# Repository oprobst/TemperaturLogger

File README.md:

# TemperaturLogger

Einfacher Temperatur Logger über ATTiny 841 und Knopfzelle.
Gemessen wird über einen TSic 506, wofür die Spannung mittels DCDC Boost auf 5V gesetzt wird.

TODO:
Sobald der Logger an USB angeschlossen wird, kann er per Bootloader neu programmiert werden oder aber die Daten ausgelesen werden.

### Bootloader TinySafeBoot
http://jtxp.org/tech/tinysafeboot.htm
gute Anleitung unter https://ladvien.github.io/robots/tsb/

./tsb tn841 b2a7

tsb COM5:4800 fw TemperaturLogger.hex

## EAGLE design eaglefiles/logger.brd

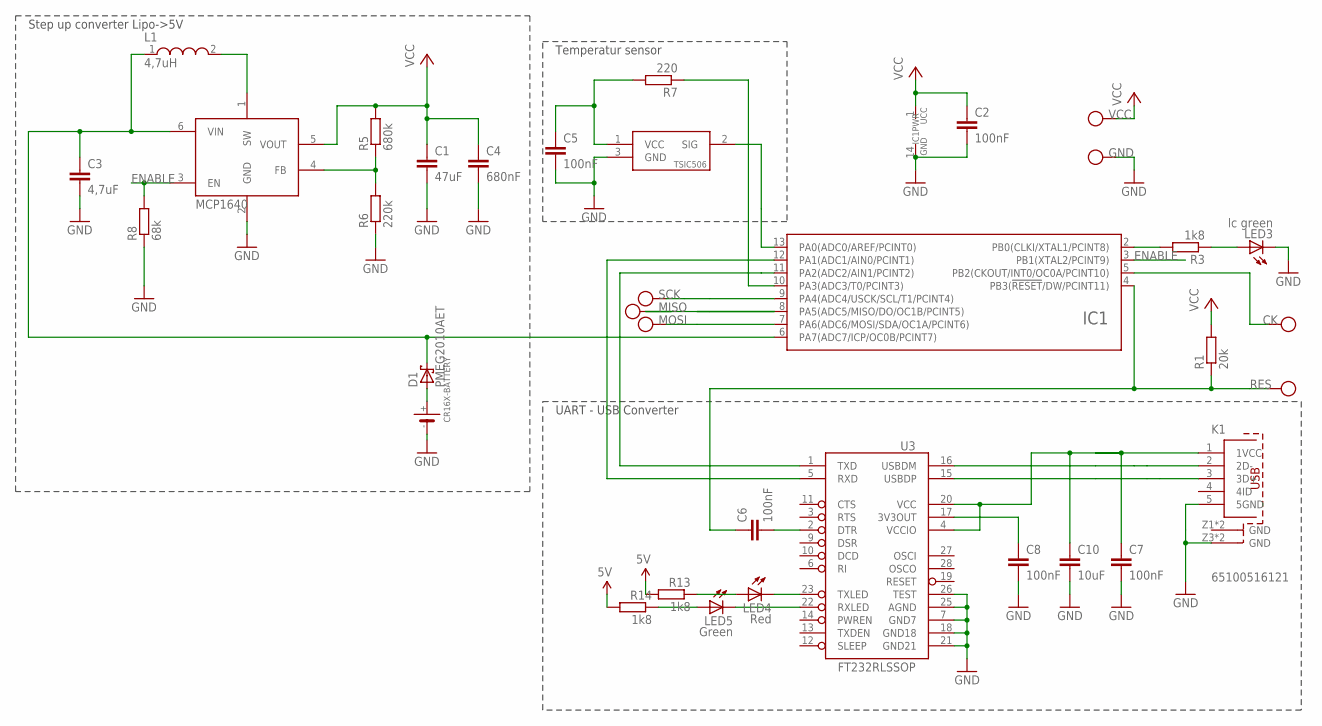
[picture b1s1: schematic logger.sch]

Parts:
C1: 47uF; C1206
C2, C7: 100nF; C1206
C3: 4,7uF; C1206
C4: 680nF; C0805
C5, C6, C8: 100nF; C0603
C10: 10uF; C1206
D1: PMEG2010AET; SOT23
IC1: ATTINY24/44/84-SSU; SOIC14
K1: 65100516121
L1: 4,7uH; WE-TPC_3816
LED3: lc green; CHIPLED_0603
LED4: Red; CHIPLED_0603
LED5: Green; CHIPLED_0603
R1: 20k; R1206
R3, R13, R14: 1k8; R1206
R5: 680k; R1206
R6: 220k; R1206
R7: 220; R1206
R8: 68k; R1206
U1: MCP1640; SOT23-6
U3: FT232RLSSOP; SSOP28DB
U$1: CR16X-BATTERY; 16MM-BATTERY-HOLDER
U$2: TSIC-506; TO92
U$7, U$8, U$9, U$10, U$11, U$12, U$13: PIN1.27; PIN-1.27

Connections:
CK: IC1.5 (PB2(CKOUT/INT0/OC0A/PCINT10)), U$13.P$1
ENABLE: IC1.3 (PB1(XTAL2/PCINT9)), R8.2, U1.3 (EN)
GND: C1.2, C2.2, C3.2, C4.2, C5.2, C7.2, C8.2, C10.2, IC1.14 (GND), K1.5 (5GND), K1.Z3 (GND), K1.Z4 (GND), LED3.C, R6.1, R8.1, U1.2 (GND), U3.7 (GND7), U3.18 (GND18), U3.21 (GND21), U3.25 (AGND), U3.26 (TEST), U$1.P$1, U$2.3 (GND), U$10.P$1
MISO: IC1.8 (PA5(ADC5/MISO/DO/OC1B/PCINT5)), U$7.P$1
MOSI: IC1.7 (PA6(ADC6/MOSI/SDA/OC1A/PCINT6)), U$11.P$1
unnamed: IC1.11 (PA2(ADC2/AIN1/PCINT2)), U3.1 (TXD)
unnamed: IC1.13 (PA0(ADC0/AREF/PCINT0)), U$2.2 (SIG)
unnamed: C8.1, U3.17 (3V3OUT)
unnamed: LED4.A, R13.1
unnamed: R5.1, R6.2, U1.4 (FB)
unnamed: D1.1 (A), U$1.P$2
unnamed: LED5.A, R14.1
unnamed: C6.2, U3.2 (DTR)
unnamed: IC1.10 (PA3(ADC3/T0/PCINT3)), R7.1
unnamed: C5.1, R7.2, U$2.1 (VCC)
unnamed: LED3.A, R3.1
unnamed: IC1.12 (PA1(ADC1/AIN0/PCINT1)), U3.5 (RXD)
RES: C6.1, IC1.4 (PB3(!RESET!/DW/PCINT11)), R1.1, U$9.P$1
RXLED: LED5.C, U3.22 (RXLED)
SCK: IC1.9 (PA4(ADC4/USCK/SCL/T1/PCINT4)), U$8.P$1
SW: L1.2, U1.1 (SW)
TXLED: LED4.C, U3.23 (TXLED)
USB_D+: K1.3 (3D+), U3.15 (USBDP)
USB_D-: K1.2 (2D-), U3.16 (USBDM)
V+: IC1.2 (PB0(CLKI/XTAL1/PCINT8)), R3.2
VCC: C1.1, C2.1, C4.1, IC1.1 (UCC), R1.2, R5.2, U1.5 (VOUT), U$12.P$1
VSUPPLY: C3.1, D1.3 (C), IC1.6 (PA7(ADC7/ICP/OC0B/PCINT7)), L1.1, U1.6 (VIN)
V_USB: C7.1, C10.1, K1.1 (1VCC), R13.2, R14.2, U3.4 (VCCIO), U3.20 (VCC)

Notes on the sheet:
Step up converter Lipo->5V
Temperatur sensor
UART - USB Converter

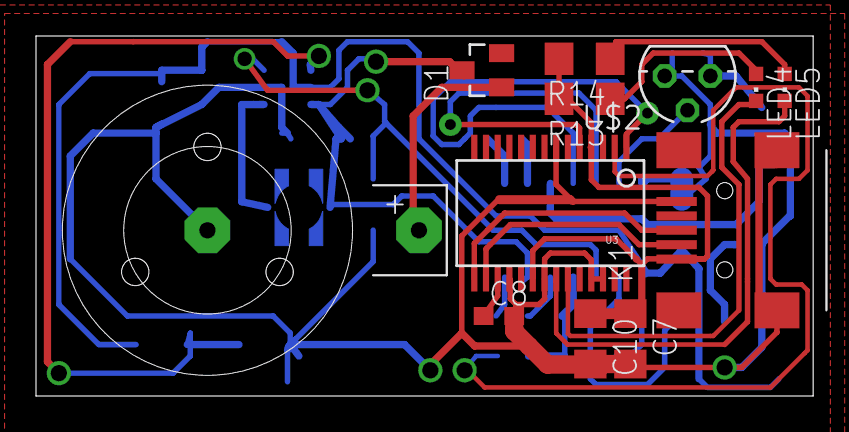
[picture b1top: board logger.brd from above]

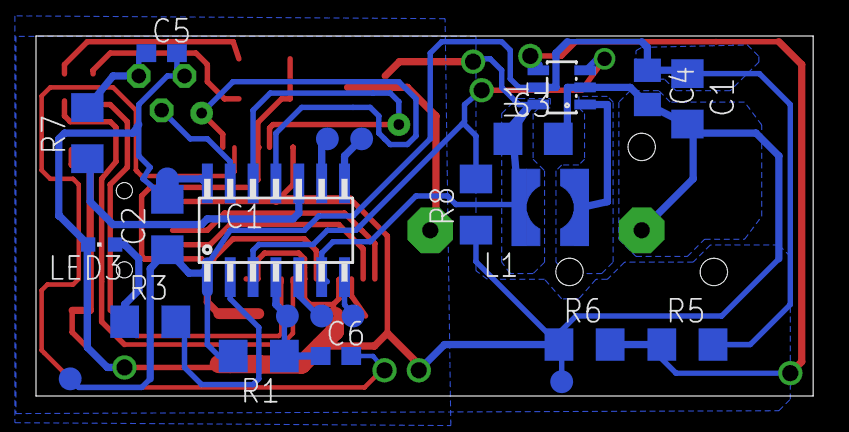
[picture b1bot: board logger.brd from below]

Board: 2 copper layers, 43.2 x 20.0 mm, 35 parts (23 on the bottom side), 28 nets.

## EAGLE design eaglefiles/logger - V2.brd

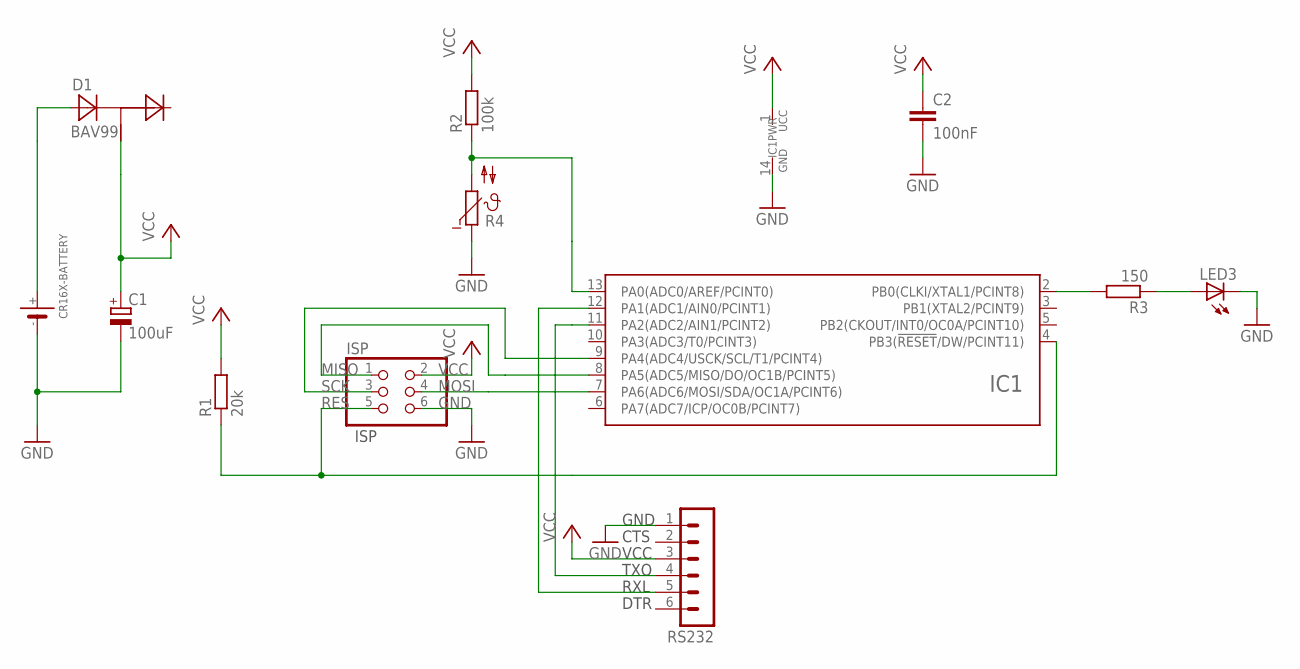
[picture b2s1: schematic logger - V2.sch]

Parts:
C1: 100uF; 153CLV-0505
C2: 100nF; C1206K
D1: BAV99; SOT-23
IC1: ATTINY24/44/84-SSU; SOIC14
ISP: PINHD-2X3; 2X03
LED3: LED3MM
R1: 20k; R1206
R2: 100k; R1206
R3: 150; R1206
R4: NTC640; P640
RS232: MA06-1
U$1: CR16X-BATTERY; 16MM-BATTERY-HOLDER

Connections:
D1: D1.3 (A), U$1.P$2
GND: C1.-, C2.2, IC1.14 (GND), ISP.6, LED3.K (C), R4.1, RS232.1, U$1.P$1
MISO: IC1.8 (PA5(ADC5/MISO/DO/OC1B/PCINT5)), ISP.1
MOSI: IC1.7 (PA6(ADC6/MOSI/SDA/OC1A/PCINT6)), ISP.4
unnamed: IC1.11 (PA2(ADC2/AIN1/PCINT2)), RS232.4
unnamed: IC1.13 (PA0(ADC0/AREF/PCINT0)), R2.1, R4.2
unnamed: LED3.A, R3.1
unnamed: IC1.12 (PA1(ADC1/AIN0/PCINT1)), RS232.5
RES: IC1.4 (PB3(!RESET!/DW/PCINT11)), ISP.5, R1.1
SCK: IC1.9 (PA4(ADC4/USCK/SCL/T1/PCINT4)), ISP.3
V+: IC1.2 (PB0(CLKI/XTAL1/PCINT8)), R3.2
VCC: C1.+, C2.1, D1.1 (M), IC1.1 (UCC), ISP.2, R1.2, R2.2, RS232.3

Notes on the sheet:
DTR
RXL
TXO
VCC
CTS
GND
ISP

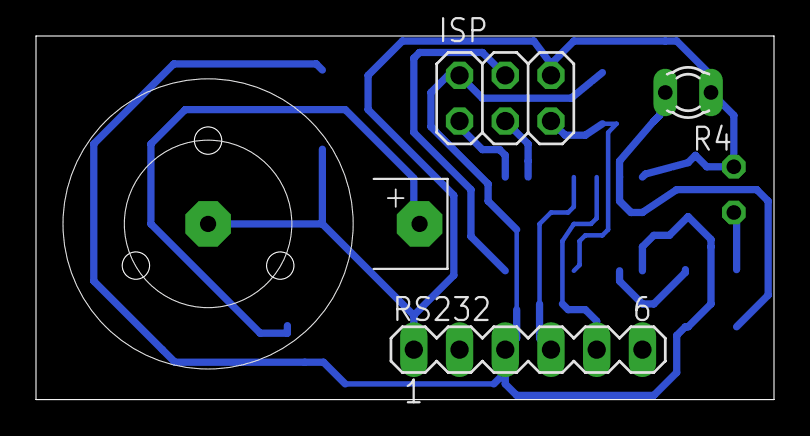
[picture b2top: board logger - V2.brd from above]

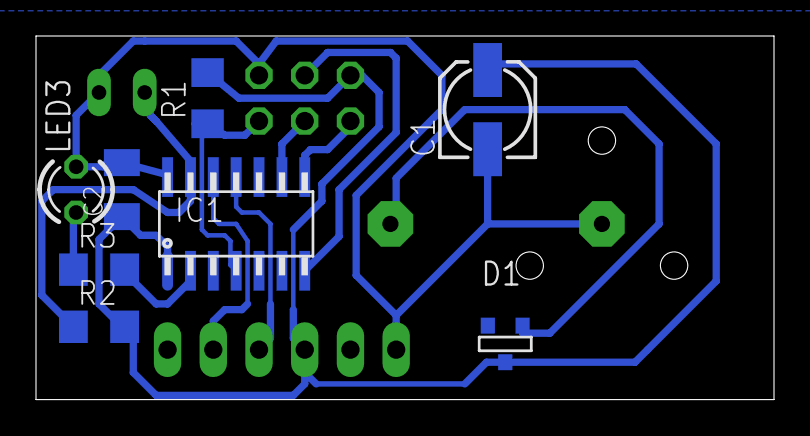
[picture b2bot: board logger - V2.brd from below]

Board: 2 copper layers, 41.0 x 20.2 mm, 12 parts (8 on the bottom side), 12 nets.

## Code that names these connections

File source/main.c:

#include "main.h"

volatile uint32_t secondsSinceLastMeasurement = 0;
int32_t temperature = 0;

ISR (TIMER1_COMPA_vect) {
	secondsSinceLastMeasurement++;
}

/************************************************************************/
/* Main                                                                 */
/************************************************************************/
int main( void )
{
	//Outputs:
	//PB0: LED
	//PB1: 5V supply power enable
	DDRB |= (1 << PB0 | 1 << PB1);
	//PA3: Power up supply sensor
	DDRA |= (1 << PA3);

//test
	//Clock on PB2
	//CLKCR |= (1 << CKOUTC);	
	//set_start_temperature(5);
	//set_end_temperature(30);
	//set_resolution(1);
	//set_intervall(180);
//endoftest
	
	init_adc();
	init_interrupts ();
	init_converter();
	TSIC_INIT();	// Init TSIC Temperatursensor
	
	sei();
	_delay_ms(1000);
	
	uint16_t supplyVolt = measure_supply_voltage();
	
	//measure_mode(); //outcomment me to debug on pc
	
	if (supplyVolt < 4500 && supplyVolt > 1000){
		// Set UART pins to 0, to prevent reverse voltage from ft232 VCC pin (~ 1V if RX/TX = Hi)
		DDRA |= (1 << PA1 | 1 << PA2);
		PORTA |= (0 << PA1  | 0 << PA2);
		measure_mode();
		} else{
		uart_init();
		output_mode ();
	}
}



void power_down(){
	set_sleep_mode(SLEEP_MODE_PWR_DOWN);
	sleep_enable();
	sleep_cpu();
	sleep_disable();
}

void idle(){
	ACSR1A |= ((1 << ACD1) ); //disable ac
	ACSR1A |= ((1 << ACD1) ); //disable ac
	set_sleep_mode(SLEEP_MODE_IDLE);
	sleep_enable();
	sleep_cpu();
	sleep_disable();
}


void measure_mode(){
	for (uint8_t i = 0; i < 26; i++){
		PORTB ^= (1<<PB0);
		_delay_ms(200);
	}
	while(1) {
		
		if (secondsSinceLastMeasurement >= get_interval()){
			POWER_HI
			_delay_ms(2);
			PORTB ^= (1<<PB0);
			ACSR1A |= ((0 << ACD1) ); //enable ac
			ACSR0A |= ((0 << ACD1) ); //enable ac
			uint16_t temp;
			getTSicTemp(&temp);
			uint32_t write = to_units(temp);
			write_next_value(write);
			POWER_LO
			PORTB ^= (1<<PB0);
			
			if (is_buffer_full()){
				while(1)
				{
					power_down();
				}
			}
			secondsSinceLastMeasurement = 0;
			idle ();
		}
		
	}
}

void output_mode (){
	PORTB ^= (1<<PB0);
	//uart_transmit_string("\n\rTEMPERATURE LOGGER\n\r");
	//uart_transmit_string("\n\r USB MODE \n\r");
	print_help();
	while(1)
	{
		char command = uart_receive();
		if (command == 'T'){
			_delay_ms(0);
			if (getTSicTemp(&temperature)){ //turn the TSIC-Sensor ON -> messure -> OFF
				
				uart_transmit_string("T");
				uart_transmit_integer(temperature);
				uart_transmit_string("t");
			}
			
			} else if (command == 'C'){
			show_configuration();
			} else if (command == 'M'){
			
			uart_transmit_string("Sending EEPROM! \n\r");
			
			uint16_t nextValue = 0;
			while(! is_buffer_full()){
				nextValue = read_next_value();
				uint16_t output = to_temperatur(nextValue);
				uart_transmit_string(",");
				uart_transmit_integer(output);
			}
			uart_transmit_string(" \n\r End of EEPROM... \n\r");
			eeprom_reset_current_address();
			} else if (command == 'i'){
			set_intervall(read_config_value());
			show_configuration();
			} else if (command == 'e'){
			set_end_temperature(read_config_value());
			show_configuration();
			} else if (command == 's'){			
			set_start_temperature(read_config_value());
			show_configuration();
			} else if (command == 'r'){
			set_resolution(read_config_value());
			show_configuration();
			} else if (command == 'c'){
			clear();
			show_configuration();
			} else if (command == 'p'){
			if (get_protected_mode() == 1){
				set_protected_mode(0);
			} else{
				set_protected_mode(1);
			}
			show_configuration();
			} else {
			uart_transmit_string("Unknown \n\r");
			print_help();
		}
		
	}
}


void print_help(){
	uart_transmit_string("Valid commands: \n\r");
	uart_transmit_string(" T  => One measurement\n\r");
	uart_transmit_string(" C  => Config\n\r");
	uart_transmit_string(" M  => Memory\n\r");
	uart_transmit_string(" ixxx  => intervall in sec.\n\r");
	uart_transmit_string(" sxxx  => min C\n\r");
	uart_transmit_string(" exxx  => max C\n\r");
	uart_transmit_string(" rxxx  => res (001 or 002) \n\r");
	uart_transmit_string(" p  => protected \n\r");
}

void show_configuration(){
	uart_transmit_string("\n\r Resolution: ");
	uart_transmit_integer(get_resolution());
	uart_transmit_string("\n\r From range: ");
	uart_transmit_integer(get_start_temperature());
	uart_transmit_string("\n\r To range: ");
	uart_transmit_integer(get_end_temperature());
	uart_transmit_string("\n\r Interval : ");
	uart_transmit_integer(get_interval());
	uart_transmit_string(" sec.\n\r ");
	uart_transmit_string("\n\r protected: ");
	uart_transmit_integer(get_protected_mode());
	uart_transmit_string(" mV\n\r ");
	uart_transmit_string("\n\r Voltage : ");
	uart_transmit_integer(measure_supply_voltage());
	uart_transmit_string(" mV\n\r ");
	if (getTSicTemp(&temperature)){ 
	    uart_transmit_string("Temperature:");
		uart_transmit_integer(temperature);
		uart_transmit_string("\n\r");
	}
}
void init_interrupts (){
	//every second
	
	TCCR1B |= (1 << WGM12); // CTC Modus
	TIMSK1 |= (1<<OCIE1A); // Allow interrupt
	TCCR1B |= (0<<CS12) | (1<<CS11) | (1<<CS10); // Prescaler 64
	OCR1A = 15624;
	
}

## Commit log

2016-10-29 Initial check in of first tests
2016-10-29 Moved files
2016-10-29 Updated ignore list
2016-10-29 Changed file system layout
2016-11-03 UART-USB Adapter and TSIC-506 added
2016-11-03 Schaltplan export added
2016-11-04 Added ctr for reset
2016-11-04 Implemented EEPROM read and write
2016-11-04 Added some additional comments
2016-11-04 First temperatur log implementation
2016-11-05 Extracted extra files for adc measurement
2016-11-05 Externalized uart communication to own file
2016-11-05 Cleaned up main.c
2016-11-05 Added timer interrupts
2016-11-05 configurable interface for intervall and range
2016-11-06 Configured tinybootloader
2016-11-06 ADdded link to tinysafeboot loader
2016-11-12 Corrected direction of mosfet
2016-11-12 Corrected direction of mosfet & copied lib for tsic
2016-11-12 Added enable and disable ac when in idle mode
2016-11-12 Added diode for 5V usb port
2016-11-12 Added option to trigger 5V supply voltage only on demand
2016-11-12 Adjusted reverse voltage of uart -> FT232 VCC
2016-11-12 Adjusted uart pins to 0 in measure mode, this time really... ;-)
2016-11-15 Fixed failure in schematic: TX and RX mixed up...
2016-11-15 First include of temperature sensor, additional main.h
2016-11-17 Fixed wrong signal
2016-11-17 Inital tests for javafx logger application
2016-11-17 Added mean temperature curve
2016-11-18 Ugly implementation, but well... it works.
2016-11-18 eventhandler, small style and csv export
2016-12-08 Replaced mosfet by diode
2016-12-08 Mainly power management
2016-12-09 Option to save csv
2016-12-09 Adjusted to TSIC 516, added option to configure per uart
2016-12-09 Increased resolution
2016-12-09 Adjusted strange value detection
2016-12-20 added protected mode (still bugy)

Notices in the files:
parts and their libraries:
EagleLibrary_Wuerth_Elektronik_eiSos_rev: Copyright: Würth Elektronik
